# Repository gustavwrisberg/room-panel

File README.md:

# Universal Room Board – Room Panel

A small ESP32-C6 board for Home Assistant that turns into a wall-mounted room panel:
mmWave presence, temperature, humidity, light and CO₂ sensing, a 2.9" e-paper
display, a rotary knob and four buttons for lights, blinds and scenes. Built around
a Seeed XIAO ESP32-C6, assembled by JLCPCB, running ESPHome.

The same PCB can also drive a motorized IKEA HOPPVALS blind through the J2
expansion header (motor board, separate design).

## What's in this repo

| Folder | Contents |
| --- | --- |
| `hardware/BOM.csv` | Full bill of materials for one finished panel (PCB, modules, connectors, cables, case hardware) |
| `hardware/kicad/` | KiCad 10 project (schematic, PCB) and the JLCPCB production files |
| `hardware/render/` | Scripts that make the 3D render from the KiCad board |
| `hardware/case/` | Parametric case (CadQuery), printable STL and STEP files |
| `firmware/` | ESPHome configuration for the living-room panel |
| `docs/` | Assembly, Home Assistant setup and pin map |

## Hardware at a glance

| Part | Ref | Connection |
| --- | --- | --- |
| Seeed XIAO ESP32-C6 | U2 | Wi-Fi now, Thread later |
| DFRobot C4002 mmWave radar | J1 | UART 115200 (D6/D7), OUT → expander P4 |
| Sensirion SHT40 | U1 | I²C 0x44 |
| ROHM BH1750 | U4 | I²C 0x23 |
| SCD40/SCD41 breakout | J4 | I²C 0x62, wires soldered into J4, sits behind the display |
| NXP PCA9554 expander | U5 | I²C 0x20 – buttons, knob press, display reset, radar OUT |
| Waveshare 2.9" e-paper V2 | J3 | SPI (D8 SCK, D10 MOSI, D9 CS, D1 DC, D0 BUSY) |
| Rotary encoder BMQ22 | SW1 | D2 / D3, push → expander P1 |
| 4 × tactile buttons | SW2–SW5 | Lights P2, Blinds P5, All off P7, Scene P3 |

Board: 37 × 54 mm, 2 layers. Case: 145 × 70 × 24 mm.

## Cost (one panel, Nov 2026)

About **$78** per panel excluding shipping and VAT — see `hardware/BOM.csv`.
The JLCPCB board with all SMD parts and the XIAO is about $17 of that; the
display, CO₂ breakout and radar make up most of the rest.

## Quick start

1. Order the PCB from `hardware/kicad` (JLCPCB, top-side assembly) and the parts in `hardware/BOM.csv`.
2. Solder J1 (radar socket), J3 (display) and J4 (CO₂ socket).
3. Print the case from `hardware/case/out` – see `docs/assembly.md`.
4. Flash the firmware – see `docs/home-assistant.md`.

## Status

First board batch ordered (rev 1). Values marked **CHECK** in the case script and
firmware are estimates to verify against the real board.

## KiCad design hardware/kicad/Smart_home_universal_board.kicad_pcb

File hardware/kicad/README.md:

# KiCad project (KiCad 10)

| File | Contents |
| --- | --- |
| `Smart_home_universal_board.kicad_pro / .kicad_sch / .kicad_pcb` | Rev 1 board, 37 × 54 mm, 2 layers |
| `libs/EasyEDA.*` | The parts this board uses from the impartGUI EasyEDA library (symbols, footprints, 3D models): encoder, SHT40, BH1750, PCA9554, buttons, C4002 socket footprint |
| `libs/Seeed_Studio_XIAO_Series.*` | XIAO ESP32-C6 symbol and footprint |
| `sym-lib-table`, `fp-lib-table` | Point KiCad at `libs/` via `${KIPRJMOD}`, so the project opens on any PC |
| `production/` | Fabrication Toolkit output for JLCPCB (gerber zip, BOM, CPL, IPC netlist) |

`libs/EasyEDA.*` is copied from the original library (`E:\KicadLibrary`), trimmed
to the parts on this board. The XIAO library was extracted from the copy embedded
in the schematic and PCB.

The footprints load their 3D models from `${KICAD_3RD_PARTY}/EasyEDA.3dshapes/`.
On another PC, copy `libs/EasyEDA.3dshapes` into the folder that
`KICAD_3RD_PARTY` points to (Preferences → Configure Paths) to see them in the
3D viewer. Fabrication is not affected.

## BOM fix (Nov 2026)

C15/C16 (10 nF) and R11/R12 (10 kΩ) had the LCSC numbers of the 100 nF and 4.7 kΩ
parts. Corrected in the schematic, PCB and `production/bom.csv`:

| Ref | Value | Was | Now |
| --- | --- | --- | --- |
| C15, C16 | 10 nF 0402 | C1525 | C15195 |
| R11, R12 | 10 kΩ 0402 | C25900 | C25744 |

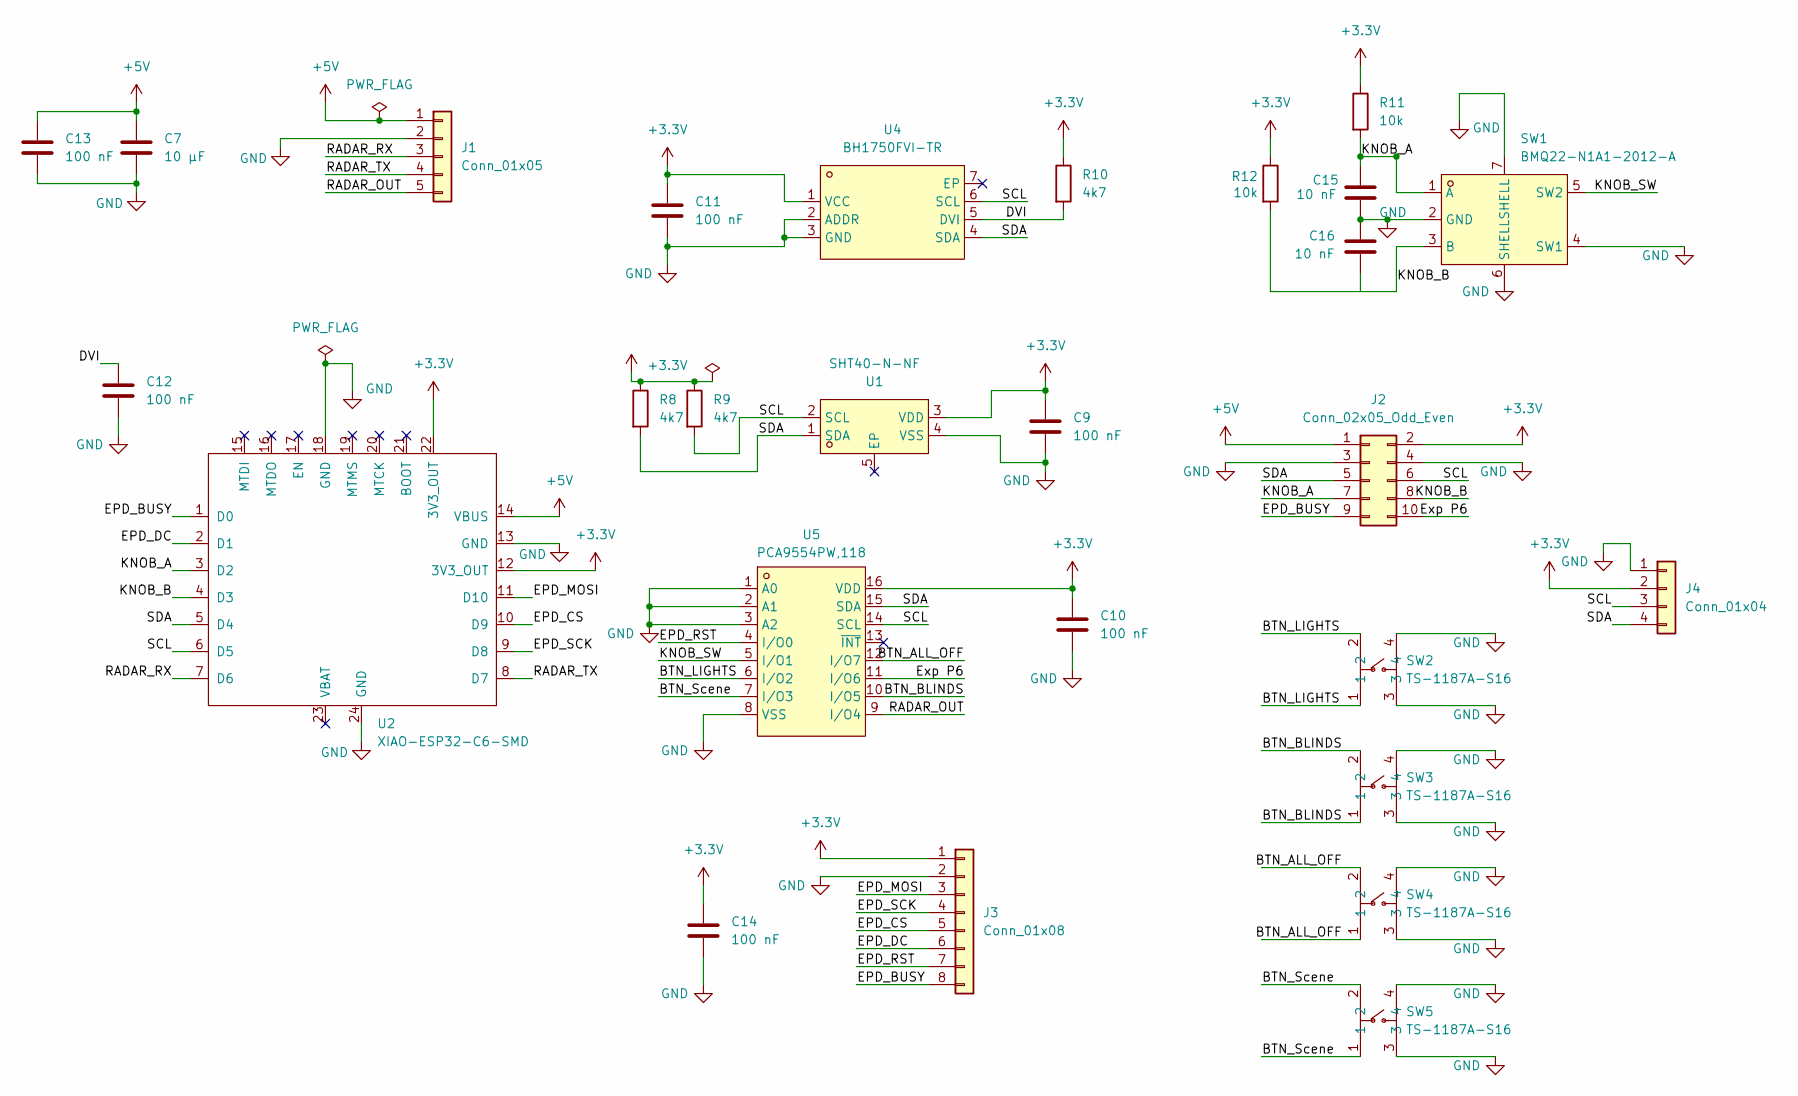
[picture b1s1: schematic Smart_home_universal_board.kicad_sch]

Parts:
C7: 10 µF; C_0805_2012Metric; LCSC Part C15850
C9, C10, C11, C12, C13, C14: 100 nF; C_0402_1005Metric; LCSC Part C1525
C15, C16: 10 nF; C_0402_1005Metric; LCSC Part C15195
J1: Conn_01x05; C4002
J2: Conn_02x05_Odd_Even; PinSocket_2x05_P2.54mm_Vertical
J3: Conn_01x08; JST_PH_B8B-PH-K_1x08_P2.00mm_Vertical
J4: Conn_01x04; PinSocket_1x04_P2.54mm_Vertical
R8, R9, R10: 4k7; R_0402_1005Metric; LCSC Part C25900
R11, R12: 10k; R_0402_1005Metric; LCSC Part C25744
SW1: BMQ22-N1A1-2012-A; SW-SMD_BMQ22-N1A1-2012-A; MPN BMQ22-N1A1-2012-A; LCSC Part C52740763
SW2, SW3, SW4, SW5: TS-1187A-S16; SW-SMD_4P-L5.1-W5.1-P3.70-LS6.5-TL_H1.5; MPN TS-1187A-S16; LCSC Part C318884
U1: SHT40-N-NF; DFN-4_L1.5-W1.5-P0.80-TL-EP; MPN SHT40-N-NF; LCSC Part C54946589
U2: XIAO-ESP32-C6-SMD; LCSC Part C27675191
U4: BH1750FVI-TR; WSOF-6_L2.6-W1.6-P0.50-TL-EP; MPN BH1750FVI-TR; LCSC Part C78960
U5: PCA9554PW,118; TSSOP-16_L5.0-W4.4-P0.65-LS6.4-BL; MPN PCA9554PW,118; LCSC Part C17230

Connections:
+3.3V: C9.1, C10.1, C11.1, C14.1, J2.2, J3.1, J4.2, R8.1, R9.1, R10.1, R11.1, R12.1, U1.3 (VDD), U2.12 (3V3_OUT), U2.22 (3V3_OUT), U4.1 (VCC), U5.16 (VDD)
+5V: C7.1, C13.1, J1.1, J2.1, U2.14 (VBUS)
/BTN_ALL_OFF: SW4.1, SW4.2, U5.12 (I/O7)
/BTN_BLINDS: SW3.1, SW3.2, U5.10 (I/O5)
/BTN_LIGHTS: SW2.1, SW2.2, U5.6 (I/O2)
/BTN_Scene: SW5.1, SW5.2, U5.7 (I/O3)
/DVI: C12.1, R10.2, U4.5 (DVI)
/EPD_BUSY: J2.9, J3.8, U2.1 (D0)
/EPD_CS: J3.5, U2.10 (D9)
/EPD_DC: J3.6, U2.2 (D1)
/EPD_MOSI: J3.3, U2.11 (D10)
/EPD_RST: J3.7, U5.4 (I/O0)
/EPD_SCK: J3.4, U2.9 (D8)
/Exp P6: J2.10, U5.11 (I/O6)
/KNOB_A: C15.1, J2.7, R11.2, SW1.1 (A), U2.3 (D2)
/KNOB_B: J2.8, R12.2, SW1.3 (B), U2.4 (D3)
/KNOB_SW: SW1.5 (SW2), U5.5 (I/O1)
/RADAR_OUT: J1.5, U5.9 (I/O4)
/RADAR_RX: J1.3, U2.7 (D6)
/RADAR_TX: J1.4, U2.8 (D7)
/SCL: J2.6, J4.3, R9.2, U1.2 (SCL), U2.6 (D5), U4.6 (SCL), U5.14 (SCL)
/SDA: J2.5, J4.4, R8.2, U1.1 (SDA), U2.5 (D4), U4.4 (SDA), U5.15 (SDA)
GND: C7.2, C9.2, C10.2, C11.2, C12.2, C13.2, C14.2, C15.2, C16.1, J1.2, J2.3, J2.4, J3.2, J4.1, SW1.2 (GND), SW1.4 (SW1), SW1.6 (SHELL), SW1.7 (SHELL), SW2.3, SW2.4, SW3.3, SW3.4, SW4.3, SW4.4, SW5.3, SW5.4, U1.4 (VSS), U2.13 (GND), U2.18 (GND), U2.24 (GND), U4.2 (ADDR), U4.3 (GND), U5.1 (A0), U5.2 (A1), U5.3 (A2), U5.8 (VSS)

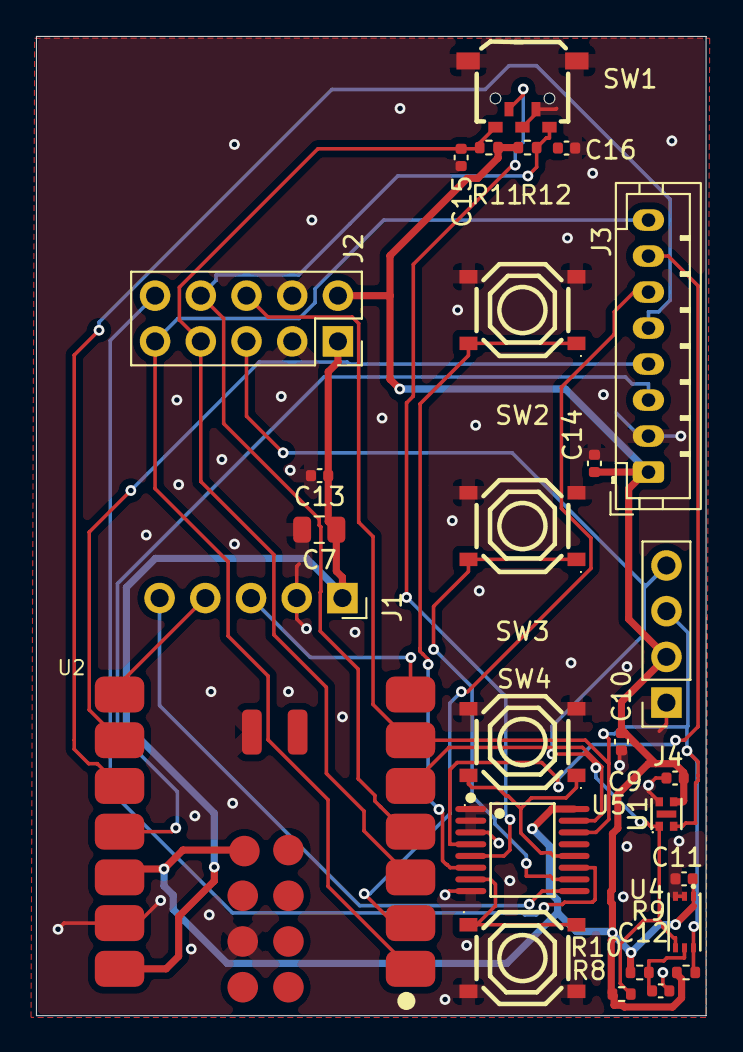
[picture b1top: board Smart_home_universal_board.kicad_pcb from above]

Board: 2 copper layers, 37.2 x 54.4 mm, 27 parts (0 on the bottom side), 23 nets.

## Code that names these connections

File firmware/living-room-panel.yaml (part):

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    components: [dfrobot_c4002]

# ---------------------------------------------------------------- buses
#  XIAO pin map:  D0 GPIO0  EPD_BUSY      D6 GPIO16 RADAR_RX (ESP TX)
#                 D1 GPIO1  EPD_DC        D7 GPIO17 RADAR_TX (ESP RX)
#                 D2 GPIO2  KNOB_A        D8 GPIO19 EPD_SCK
#                 D3 GPIO21 KNOB_B        D9 GPIO20 EPD_CS
#                 D4 GPIO22 SDA           D10 GPIO18 EPD_MOSI
#                 D5 GPIO23 SCL
i2c:
  sda: GPIO22
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    name: Knob
    internal: true
    pin_a:
      number: GPIO2       # D2 = KNOB_A (10k pull-up on board)
    pin_b:
      number: GPIO21      # D3 = KNOB_B
    resolution: 1
    on_clockwise:
      - script.execute: show_controls
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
